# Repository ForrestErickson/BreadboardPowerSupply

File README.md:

# BreadboardPowerSupply
A 5V power supply for solderless bread board designed in KiCAD V5

Screen shot PCB.

Screen shot schematic

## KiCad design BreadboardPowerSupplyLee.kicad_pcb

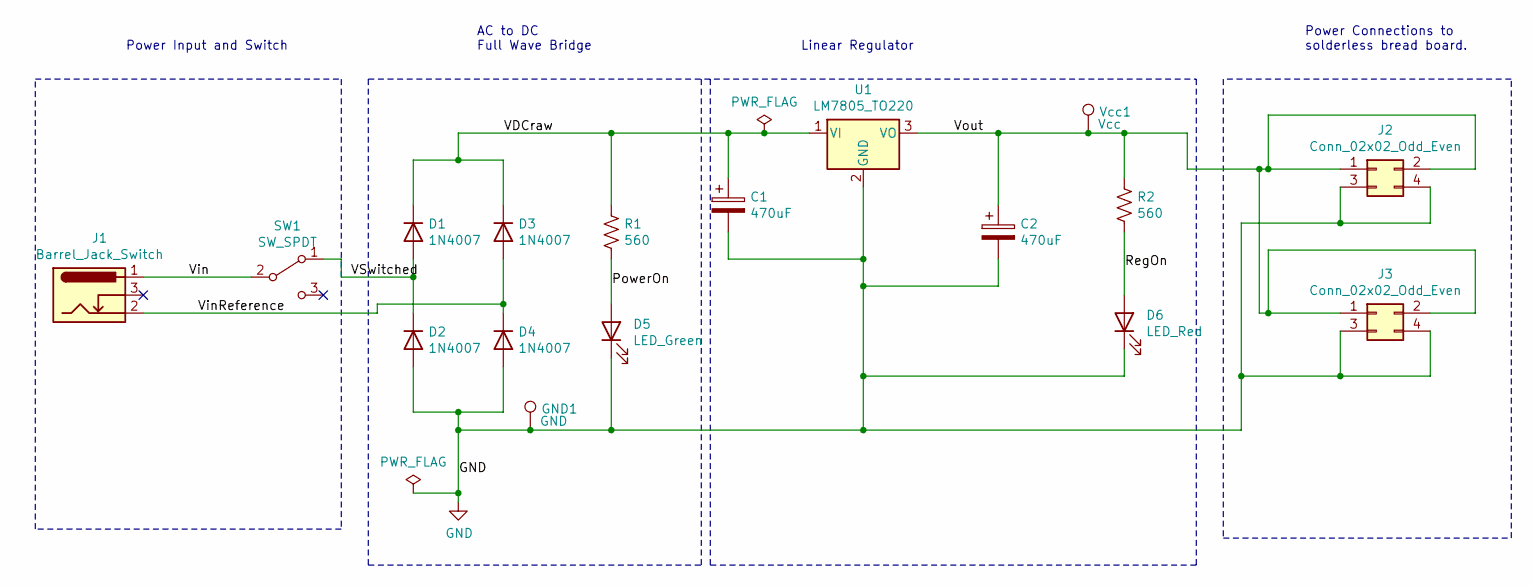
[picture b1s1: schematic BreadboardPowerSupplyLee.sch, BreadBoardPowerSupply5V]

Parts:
C1: 470uF; CP_Radial_D10.0mm_P5.00mm
C2: 470uF; CP_Radial_D6.3mm_P2.50mm
D1, D2, D3, D4: 1N4007; D_DO-41_SOD81_P10.16mm_Horizontal
D5: LED_Green; LED_D5.0mm
D6: LED_Red; LED_D5.0mm
GND1: GND; TestPoint_THTPad_2.5x2.5mm_Drill1.2mm
J1: Barrel_Jack_Switch; BarrelJack_Horizontal
J2, J3: Conn_02x02_Odd_Even; PinHeader_2x02_P2.54mm_Vertical
R1, R2: 560; R_Axial_DIN0207_L6.3mm_D2.5mm_P7.62mm_Horizontal
SW1: SW_SPDT; Switch_Slide_11.6x4mm_EG1218
U1: LM7805_TO220; TO-220-3_Vertical
Vcc1: Vcc; TestPoint_THTPad_2.5x2.5mm_Drill1.2mm

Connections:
/PowerOn: D5.2 (A), R1.2
/RegOn: D6.2 (A), R2.2
/VDCraw: C1.1, D1.1 (K), D3.1 (K), R1.1, U1.1 (VI)
/VSwitched: D1.2 (A), D2.1 (K), SW1.1 (A)
/Vin: J1.1, SW1.2 (B)
/VinReference: D3.2 (A), D4.1 (K), J1.2
/Vout: C2.1, J2.1, J2.2, J3.1, J3.2, R2.1, U1.3 (VO), Vcc1.1
GND: C1.2, C2.2, D2.2 (A), D4.2 (A), D5.1 (K), D6.1 (K), GND1.1, J2.3, J2.4, J3.3, J3.4, U1.2 (GND)

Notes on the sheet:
Power Input and Switch
AC to DC Full Wave Bridge
Linear Regulator
Power Connections to solderless bread board.

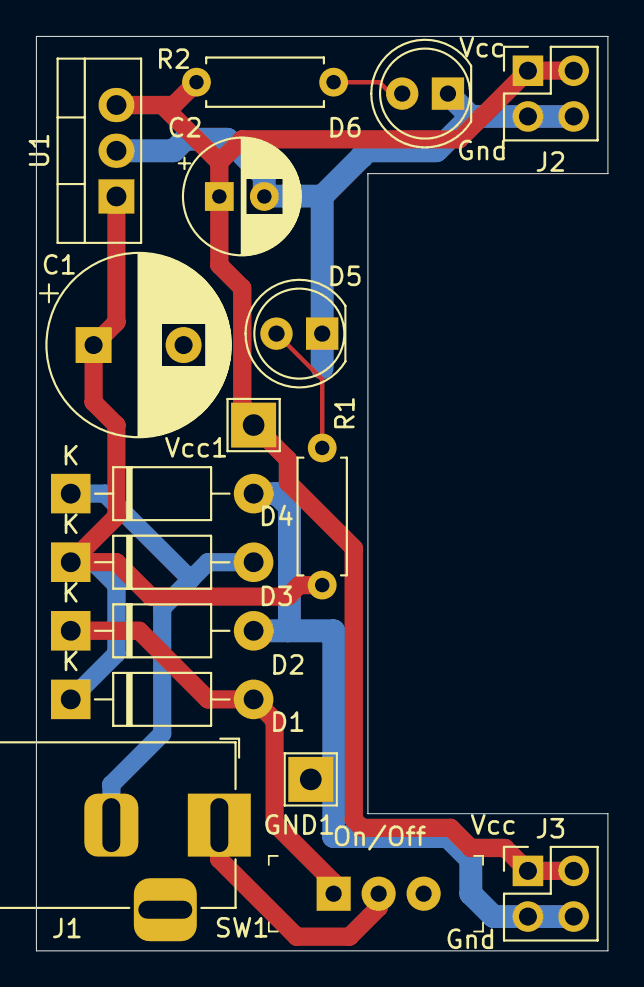
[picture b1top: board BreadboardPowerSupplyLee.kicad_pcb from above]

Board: 2 copper layers, 31.8 x 50.8 mm, 17 parts (0 on the bottom side), 8 nets.

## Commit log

2021-09-01 Initial connit. Place necessary schematic components.
2021-09-03 Update finish schematic. Start PCB with outline and place J2 and J3.
2021-09-03 Make cutaway on PCB with appropratly placed J2 and J3.
2021-09-03 Place J2 and J3 1.85 inches top to bottom.
2021-09-03 Place all components in board outline.
2021-09-03 Route traces. Pour ground fill on bottom.
2021-09-08 Add test point for Vcc and GND in schematic and PCB. Make gerbers. Looking good.
2021-09-09 Change test points to Vcc1 and GND1. Remove backup schematic file.
2021-10-25 Add gerbers from which PCBWAY order of SepOct 2021 was made. Add BOM
2022-09-20 Add gerbers as built. Add PDF for schematic and PCB Front.
2022-09-20 Updated project file as of 20220920 with PDF files.
2022-09-22 Add images for schematic and PCB
2022-09-22 Create README.md
    Add readme with PCB and Schematic screen shots.
2022-09-22 Photo of supply on breadboard as built.
2022-09-22 Update README.md
    Add photo of board as built.
